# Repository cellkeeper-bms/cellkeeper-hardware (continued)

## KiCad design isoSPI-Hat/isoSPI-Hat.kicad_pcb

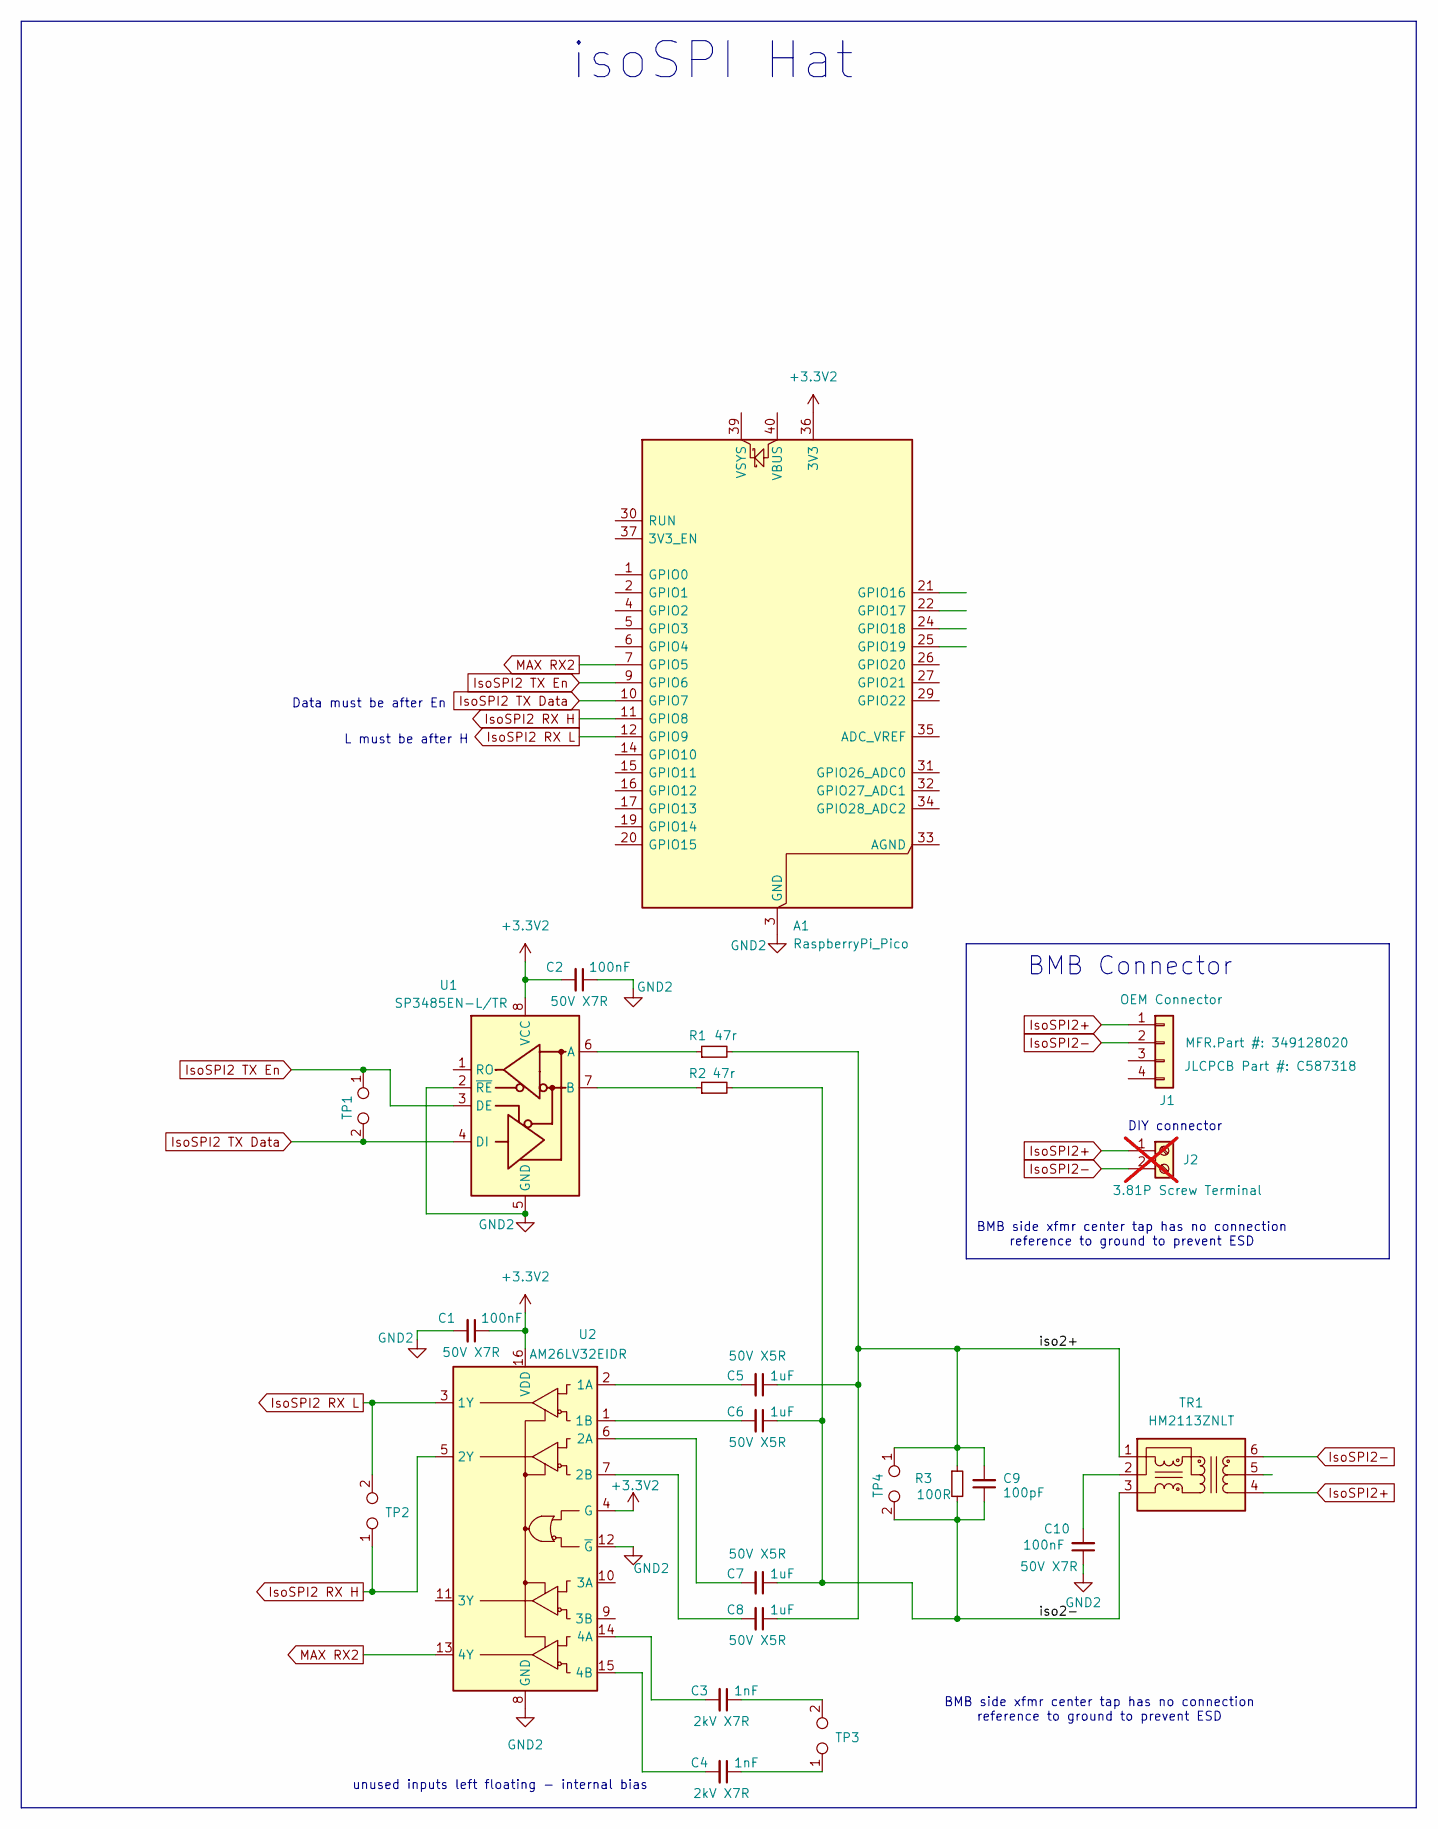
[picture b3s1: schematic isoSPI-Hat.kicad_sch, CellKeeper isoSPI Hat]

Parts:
A1: RaspberryPi_Pico; Module__RaspberryPi_Pico_Common_Unspecified
C1, C2, C10: 100nF; Capacitor_SMD__C_0603_1608Metric; JLCPCB Part # C14663
C3, C4: 1nF; Capacitor_SMD__C_1206_3216Metric; JLCPCB Part # C9196
C5, C6, C7, C8: 1uF; Capacitor_SMD__C_0603_1608Metric; JLCPCB Part # C15849
C9: 100pF; Capacitor_SMD__C_0603_1608Metric; JLCPCB Part # C14858
J1: OEM Connector; BMS_Library__CONN_SD-34912-001_02_MOL; MFR.Part # 349128020; JLCPCB Part # C587318
J2: 3.81P Screw Terminal; BMS_Library__PhoenixContact_MC_1_5_2-G-3.81_1x02_P3.81mm_Ho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; not fitted
R1, R2: 47r; Resistor_SMD__R_0603_1608Metric; JLCPCB Part # C23182
R3: 100R; Resistor_SMD__R_0603_1608Metric; JLCPCB Part # C22775
TP1, TP2, TP3, TP4: TestPoint_2Pole; BMS_Library__TestPoint_2Pads_Pitch2.54mm_Pad1.5_Drill1.0mm
TR1: HM2113ZNLT; BMS_Library__HM2113ZNLT; JLCPCB Part # C5730533
U1: SP3485EN-L/TR; Package_SO__SOIC-8_3.9x4.9mm_P1.27mm; JLCPCB Part # C8963
U2: AM26LV32EIDR; Package_SO__SOIC-16_3.9x9.9mm_P1.27mm; JLCPCB Part # C527448

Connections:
+3.3V2: A1.36 (3V3), C1.1, C2.2, U1.8 (VCC), U2.4 (G), U2.16 (VDD)
/iso2+: C5.1, C8.1, C9.2, R1.2, R3.1, TP4.1, TR1.1 (TD-)
/iso2-: C6.1, C7.1, C9.1, R2.2, R3.2, TP4.2, TR1.3 (TD+)
GND2: A1.3 (GND), A1.8 (GND), A1.13 (GND), A1.18 (GND), A1.23 (GND), A1.28 (GND), A1.38 (GND), C1.2, C2.1, C10.1, U1.2 (~RE), U1.5 (GND), U2.8 (GND), U2.12 (~G)
IsoSPI2 RX H: A1.11 (GPIO8), TP2.1, U2.5 (2Y)
IsoSPI2 RX L: A1.12 (GPIO9), TP2.2, U2.3 (1Y)
IsoSPI2 TX Data: A1.10 (GPIO7), TP1.2, U1.4 (DI)
IsoSPI2 TX En: A1.9 (GPIO6), TP1.1, U1.3 (DE)
IsoSPI2+: J1.1, J2.1, TR1.4 (TX+)
IsoSPI2-: J1.2, J2.2, TR1.6 (TX-)
MAX RX2: A1.7 (GPIO5), U2.13 (4Y)
unnamed: C3.1, TP3.2
unnamed: C4.1, TP3.1
unnamed: C10.2, TR1.2 (C_TD)
unnamed: R1.1, U1.6 (A)
unnamed: R2.1, U1.7 (B)
unnamed: C5.2, U2.2 (1A)
unnamed: C6.2, U2.1 (1B)
unnamed: C7.2, U2.6 (2A)
unnamed: C8.2, U2.7 (2B)
unnamed: C3.2, U2.14 (4A)
unnamed: C4.2, U2.15 (4B)

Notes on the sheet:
L must be after H
BMB Connector
BMB side xfmr center tap has no connection reference to ground to prevent ESD
Data must be after En
isoSPI Hat
DIY connector
unused inputs left floating - internal bias

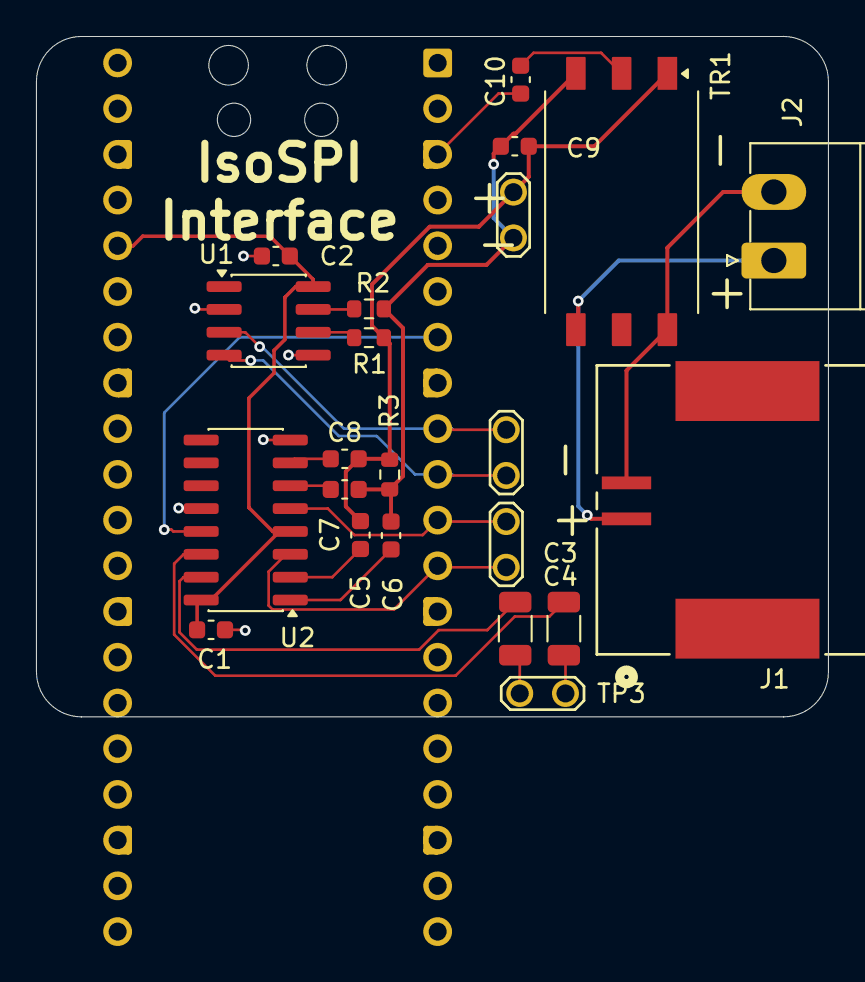
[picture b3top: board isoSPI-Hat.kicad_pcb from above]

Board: 4 copper layers, 44.0 x 37.8 mm, 23 parts (1 on the bottom side), 22 nets.
